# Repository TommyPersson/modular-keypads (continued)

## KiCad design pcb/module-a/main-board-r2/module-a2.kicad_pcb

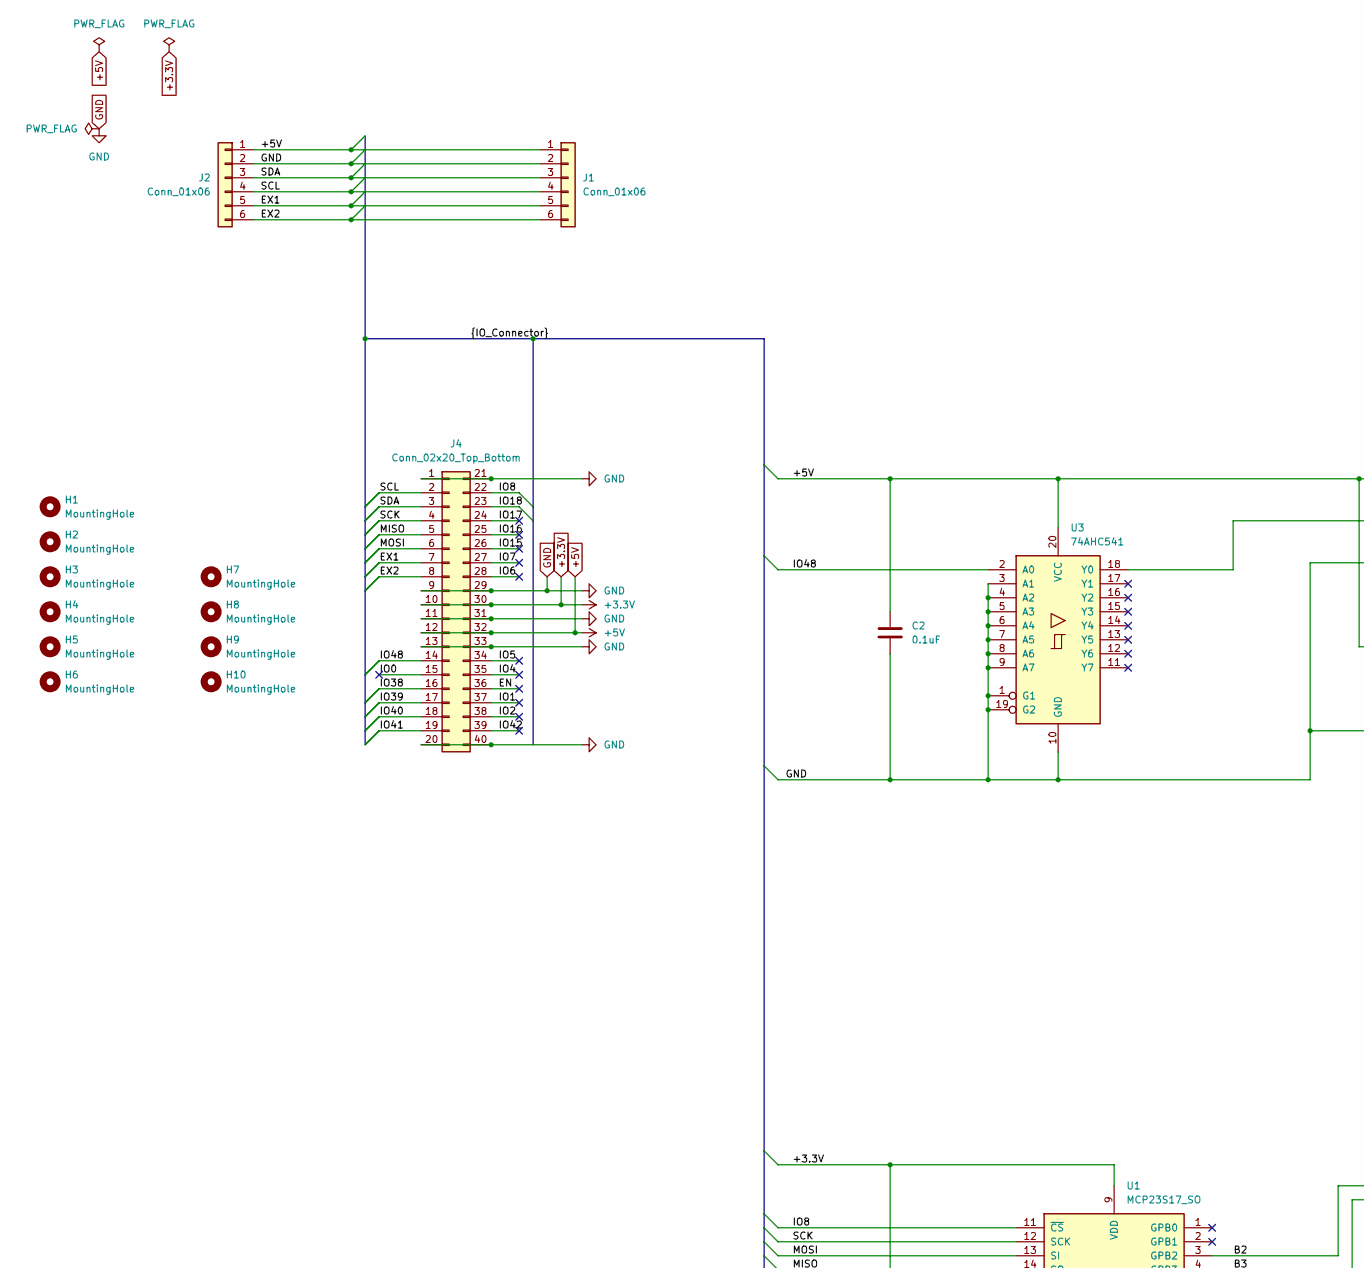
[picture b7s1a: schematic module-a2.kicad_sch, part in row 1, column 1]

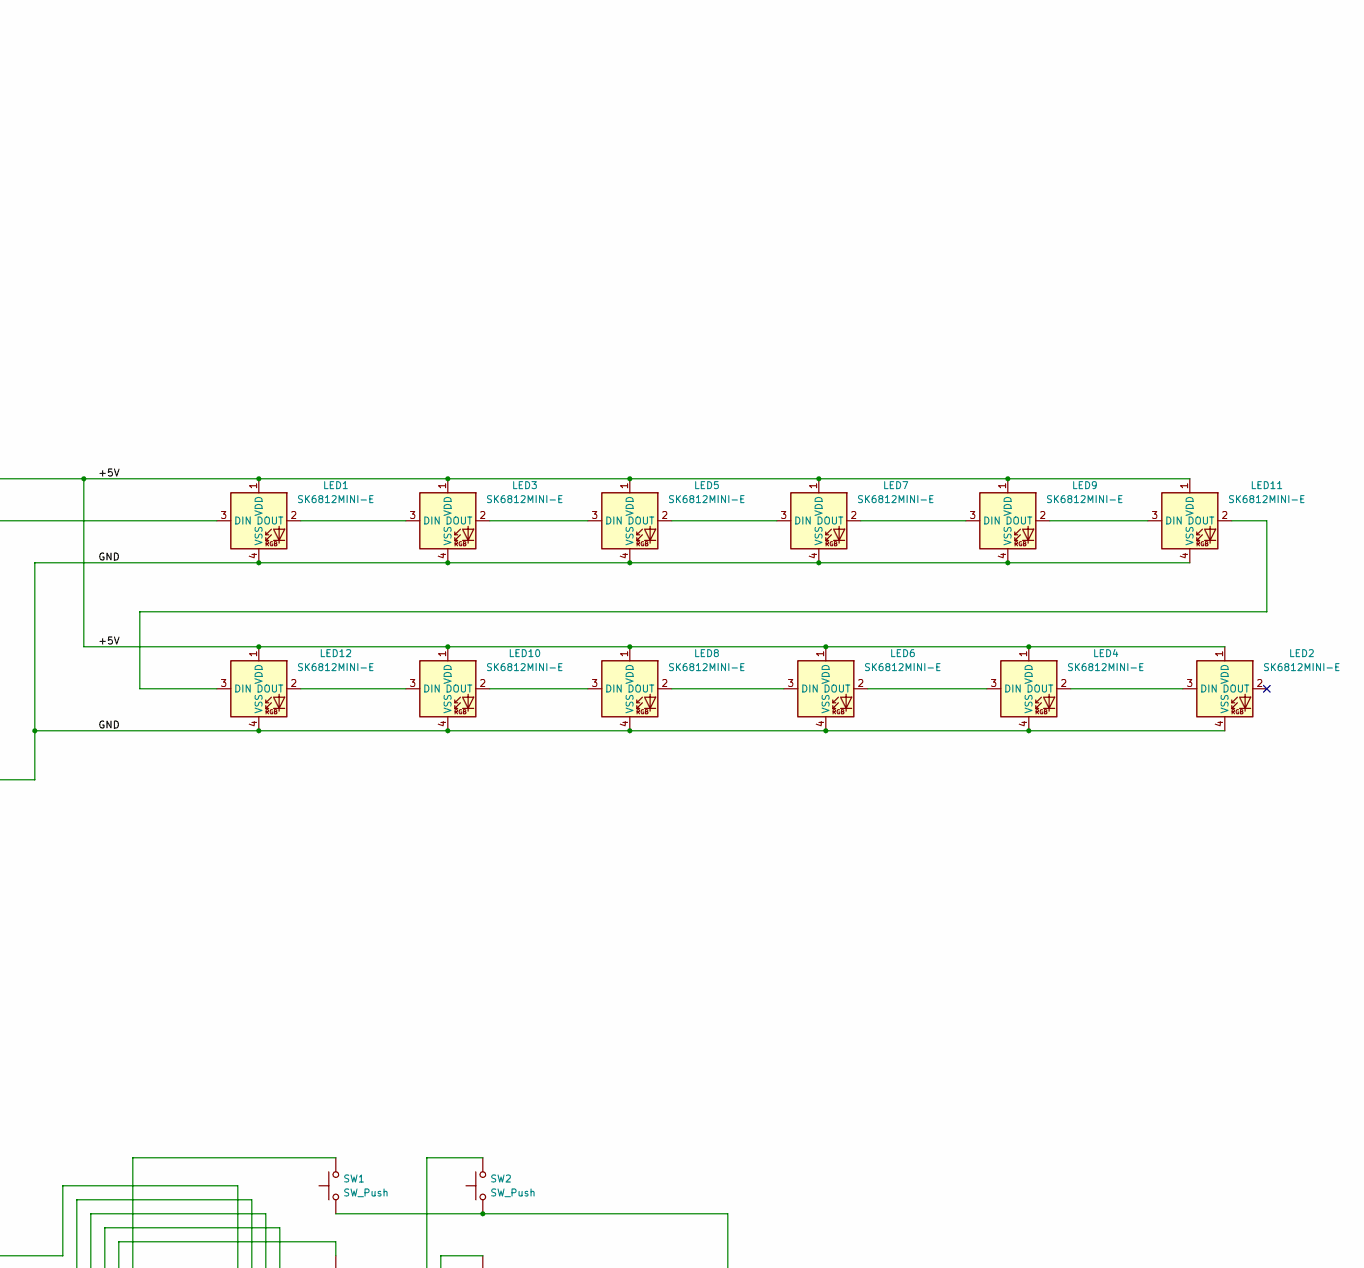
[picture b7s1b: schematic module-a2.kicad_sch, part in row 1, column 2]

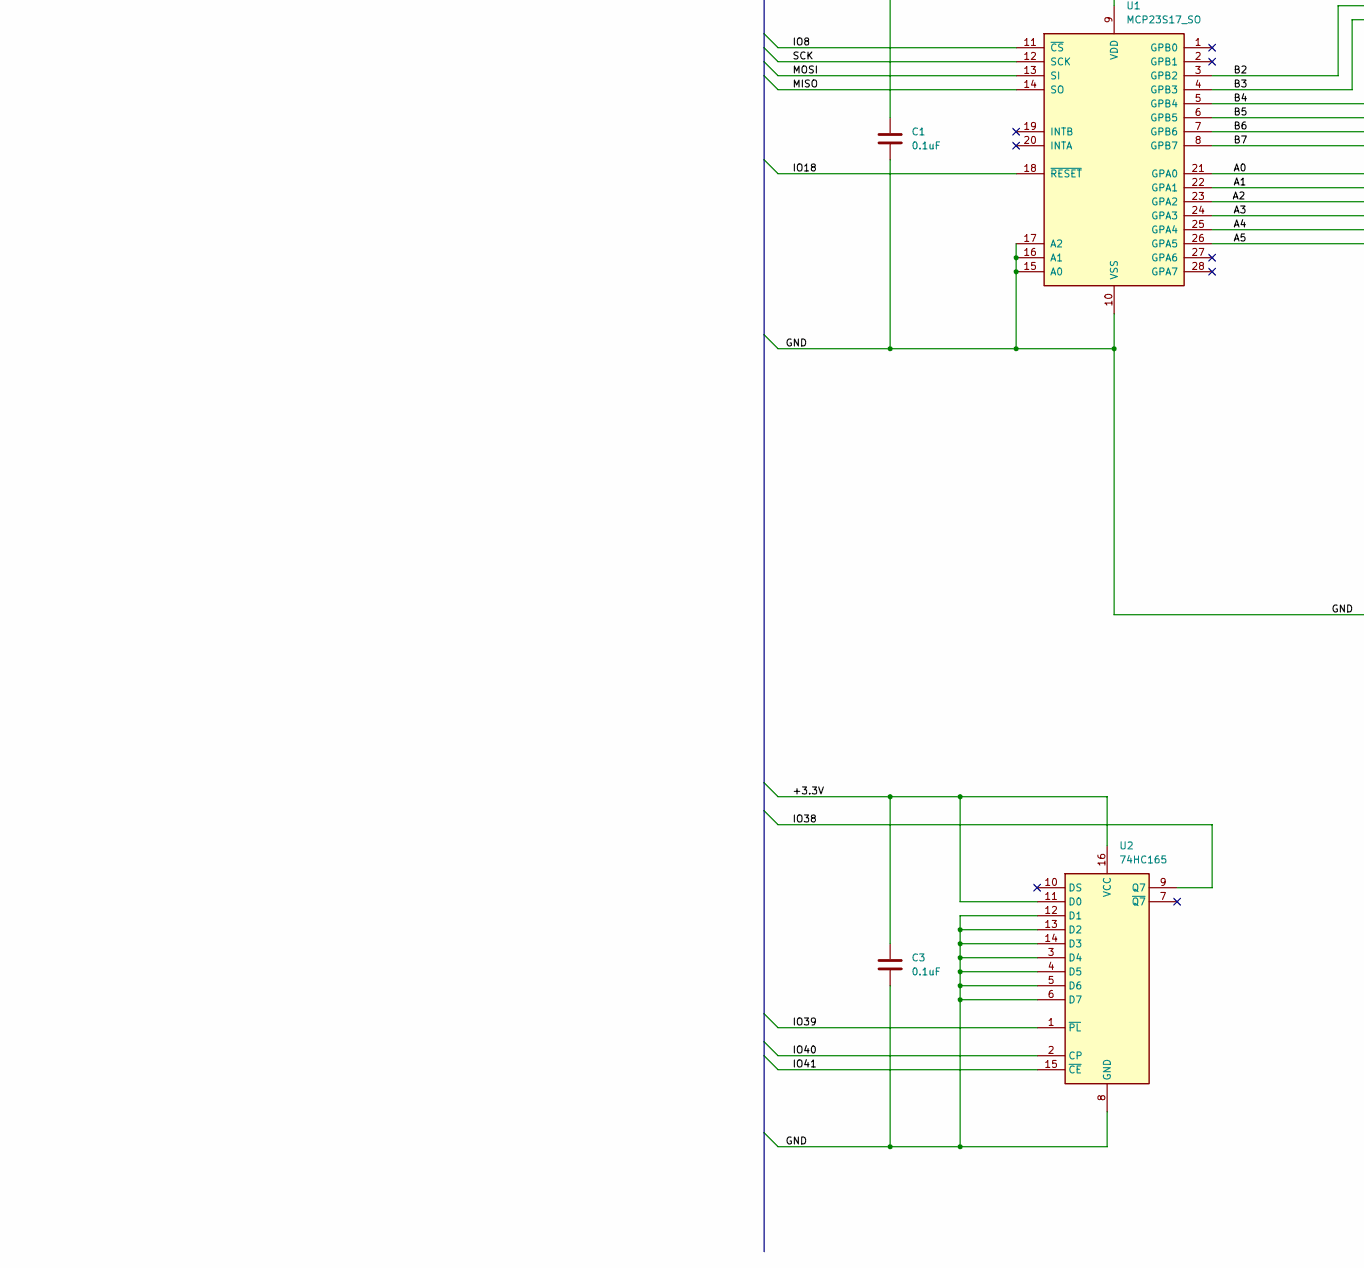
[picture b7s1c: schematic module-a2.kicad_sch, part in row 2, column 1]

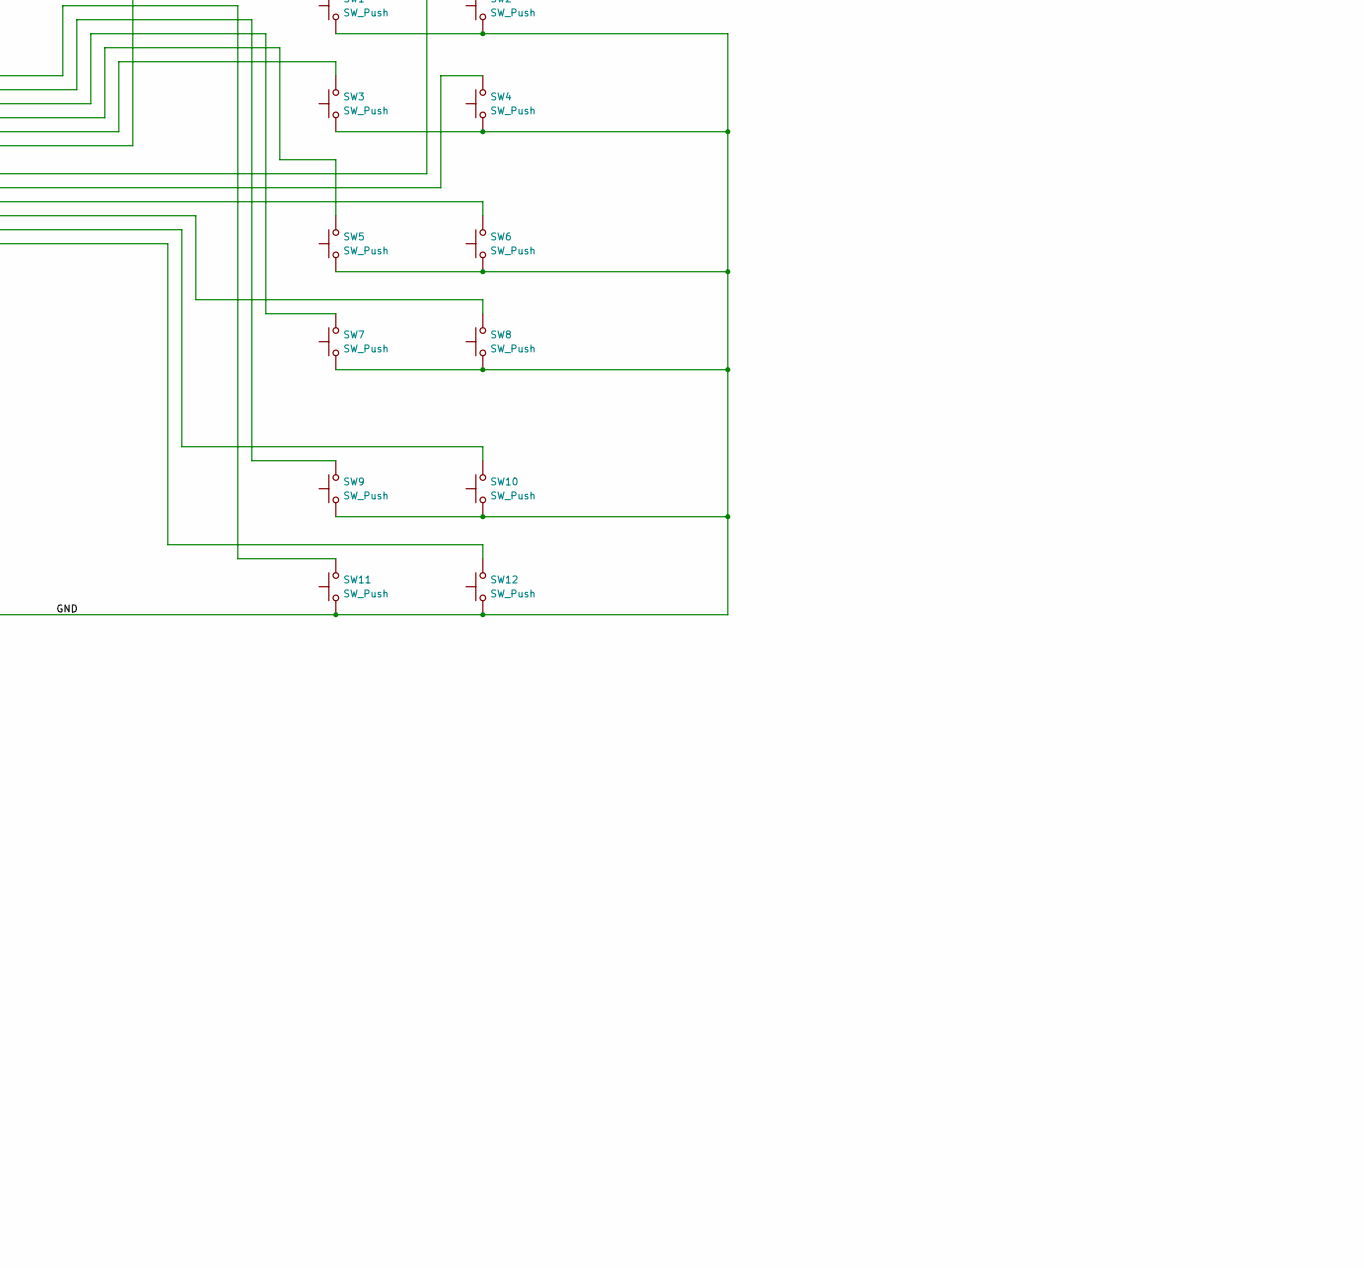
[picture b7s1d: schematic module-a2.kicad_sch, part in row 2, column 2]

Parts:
C1, C2, C3: 0.1uF; C_1206_3216Metric_Pad1.33x1.80mm_HandSolder
H1, H2, H3, H4, H5, H6: MountingHole; MountingHole_2.2mm_M2
H7, H8, H9, H10: MountingHole; MountingHole_3.7mm_Pad_TopOnly
J1: Conn_01x06; PinSocket_1x06_P2.54mm_MagPogoHor
J2: Conn_01x06; PinSocket_1x06_P2.54mm_MagPogoHor_R
J4: Conn_02x20_Top_Bottom; Hirose_DF12_DF12E3.0-40DP-0.5V_2x20_P0.50mm_Vertical
LED1, LED2, LED3, LED4, LED5, LED6, LED7, LED8, LED9, LED10, LED11, LED12: SK6812MINI-E; LED_choc_6028R-ROT
SW1, SW2, SW3, SW4, SW5, SW6, SW7, SW8, SW9, SW10, SW11, SW12: SW_Push; SW_Hotswap_Kailh_Choc_V1_1.50u
U1: MCP23S17_SO; SOIC-28W_7.5x17.9mm_P1.27mm
U2: 74HC165; SOIC-16_3.9x9.9mm_P1.27mm
U3: 74AHC541; SOIC-20W_7.5x12.8mm_P1.27mm

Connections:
+3.3V: C1.1, C3.1, J4.10, J4.30, U1.9 (VDD), U2.11 (D0), U2.16 (VCC)
+5V: C2.1, J1.1, J2.1, J4.12, J4.32, LED1.1 (VDD), LED2.1 (VDD), LED3.1 (VDD), LED4.1 (VDD), LED5.1 (VDD), LED6.1 (VDD), LED7.1 (VDD), LED8.1 (VDD), LED9.1 (VDD), LED10.1 (VDD), LED11.1 (VDD), LED12.1 (VDD), U3.20 (VCC)
/A0: SW2.2, U1.21 (GPA0)
/A1: SW4.2, U1.22 (GPA1)
/A2: SW6.2, U1.23 (GPA2)
/A3: SW8.2, U1.24 (GPA3)
/A4: SW10.2, U1.25 (GPA4)
/A5: SW12.2, U1.26 (GPA5)
/B2: SW11.2, U1.3 (GPB2)
/B3: SW9.2, U1.4 (GPB3)
/B4: SW7.2, U1.5 (GPB4)
/B5: SW5.2, U1.6 (GPB5)
/B6: SW3.2, U1.7 (GPB6)
/B7: SW1.2, U1.8 (GPB7)
/EN: J4.36
/EX1: J1.5, J2.5, J4.7
/EX2: J1.6, J2.6, J4.8
/IO0: J4.15
/IO1: J4.37
/IO2: J4.38
/IO4: J4.35
/IO5: J4.34
/IO6: J4.28
/IO7: J4.27
/IO8: J4.22, U1.11 (~CS)
/IO15: J4.26
/IO16: J4.25
/IO17: J4.24
/IO18: J4.23, U1.18 (~RESET)
/IO38: J4.16, U2.9 (Q7)
/IO39: J4.17, U2.1 (~PL)
/IO40: J4.18, U2.2 (CP)
/IO41: J4.19, U2.15 (~CE)
/IO42: J4.39
/IO48: J4.14, U3.2 (A0)
/MISO: J4.5, U1.14 (SO)
/MOSI: J4.6, U1.13 (SI)
/SCK: J4.4, U1.12 (SCK)
/SCL: J1.4, J2.4, J4.2
/SDA: J1.3, J2.3, J4.3
GND: C1.2, C2.2, C3.2, J1.2, J2.2, J4.1, J4.9, J4.11, J4.13, J4.20, J4.21, J4.29, J4.31, J4.33, J4.40, LED1.4 (VSS), LED2.4 (VSS), LED3.4 (VSS), LED4.4 (VSS), LED5.4 (VSS), LED6.4 (VSS), LED7.4 (VSS), LED8.4 (VSS), LED9.4 (VSS), LED10.4 (VSS), LED11.4 (VSS), LED12.4 (VSS), SW1.1, SW2.1, SW3.1, SW4.1, SW5.1, SW6.1, SW7.1, SW8.1, SW9.1, SW10.1, SW11.1, SW12.1, U1.10 (VSS), U1.15 (A0), U1.16 (A1), U1.17 (A2), U2.3 (D4), U2.4 (D5), U2.5 (D6), U2.6 (D7), U2.8 (GND), U2.12 (D1), U2.13 (D2), U2.14 (D3), U3.1 (G1), U3.3 (A1), U3.4 (A2), U3.5 (A3), U3.6 (A4), U3.7 (A5), U3.8 (A6), U3.9 (A7), U3.10 (GND), U3.19 (G2)
unnamed: LED1.3 (DIN), U3.18 (Y0)
unnamed: LED1.2 (DOUT), LED3.3 (DIN)
unnamed: LED2.3 (DIN), LED4.2 (DOUT)
unnamed: LED3.2 (DOUT), LED5.3 (DIN)
unnamed: LED4.3 (DIN), LED6.2 (DOUT)
unnamed: LED5.2 (DOUT), LED7.3 (DIN)
unnamed: LED6.3 (DIN), LED8.2 (DOUT)
unnamed: LED7.2 (DOUT), LED9.3 (DIN)
unnamed: LED10.3 (DIN), LED12.2 (DOUT)
unnamed: LED8.3 (DIN), LED10.2 (DOUT)
unnamed: LED9.2 (DOUT), LED11.3 (DIN)
unnamed: LED11.2 (DOUT), LED12.3 (DIN)

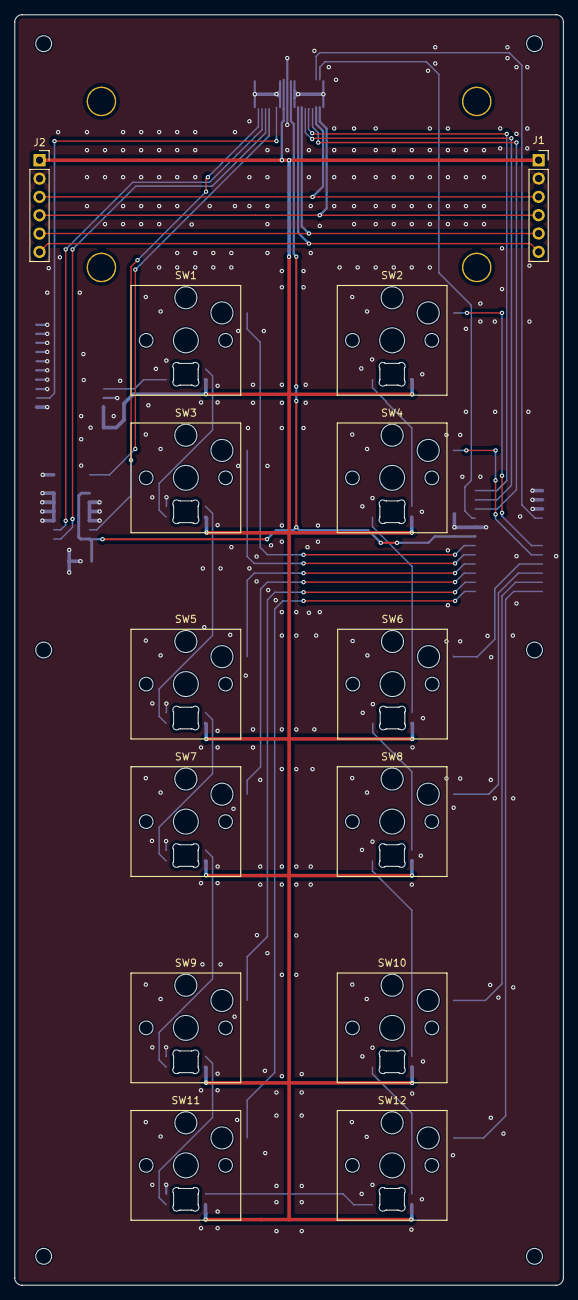
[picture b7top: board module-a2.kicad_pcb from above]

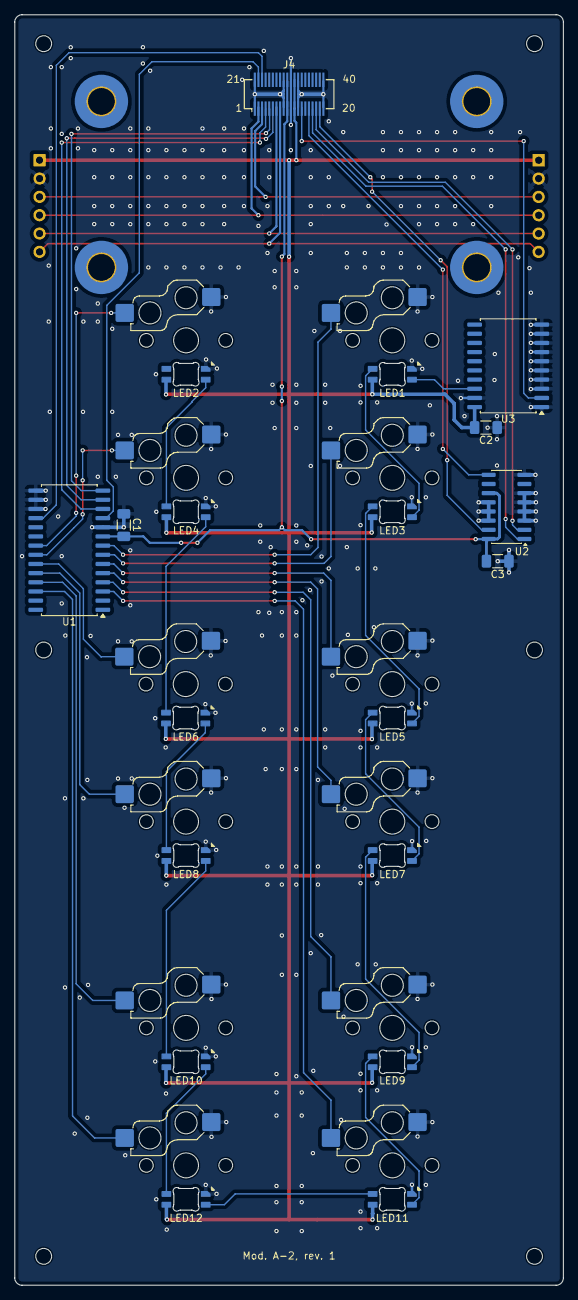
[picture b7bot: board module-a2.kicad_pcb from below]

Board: 2 copper layers, 76.0 x 176.0 mm, 43 parts (23 on the bottom side), 41 nets.

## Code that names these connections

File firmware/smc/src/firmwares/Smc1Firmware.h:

#pragma once

#include <pins_arduino.h>

#include "Firmware.h"
#include "hal/buttons/PushButtonWithIndicator.h"

namespace smc::firmwares {
    class Smc1Firmware : public Firmware {
    public:
        Smc1Firmware();
        ~Smc1Firmware() override;

        uint8_t deviceType() override { return 0x01; }

    protected:
        void doSetup() override;
        void doUpdate(uint32_t deltaUs, events::EventQueue& queue) override;
        int8_t ledIndexForButton(uint8_t buttonNumber) override;


    private:
        hal::buttons::PushButtonWithIndicator buttons[4] = {
            hal::buttons::PushButtonWithIndicator(1, PIN_PA3, leds, 0),
            hal::buttons::PushButtonWithIndicator(2, PIN_PA4, leds, 1),
            hal::buttons::PushButtonWithIndicator(3, PIN_PB0, leds, 3),
            hal::buttons::PushButtonWithIndicator(4, PIN_PB1, leds, 2),
        };
    };
}

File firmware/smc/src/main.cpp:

#include <tinyNeoPixel.h>

#include "firmwares/Firmware.h"
#include "firmwares/FirmwareFactory.h"
#include "hal/identity/DeviceId.h"
#include "hal/identity/DeviceName.h"
#include "hal/spi/SpiSlave.h"

namespace {
    auto firmwareFactory = smc::firmwares::FirmwareFactory(
        {
            .pinQ = PIN_PB3,
            .pinCLK = PIN_PB6,
            .pinCE = PIN_PB4,
            .pinLD = PIN_PB5,
        }
    );

    smc::hal::spi::SpiSlave spiSlave;
    smc::hal::identity::DeviceNameStorage deviceNameStorage;
    smc::firmwares::Firmware* firmware = nullptr;
    smc::events::EventQueue eventQueue;

    uint32_t prevUs = 0;
}

void setup() {
    Serial.swap(1);
    Serial.begin(9600);

    firmware = firmwareFactory.create();
    firmware->setup();

    uint8_t deviceId[smc::hal::identity::DEVICE_ID_LENGTH];
    smc::hal::identity::computeDeviceId(deviceId);
    spiSlave.setDeviceId(deviceId);

    uint8_t deviceName[smc::hal::identity::DEVICE_NAME_LENGTH];
    deviceNameStorage.load(deviceName);
    spiSlave.setDeviceName(deviceName);
    Serial.printf("Device name: %s\r\n", reinterpret_cast<const char*>(deviceName));

    spiSlave.setup();
    spiSlave.setDeviceType(firmware->deviceType());
    spiSlave.enqueueEvent({.type = smc::events::types::BOOTED});
}


void processCommand(const smc::hal::spi::Command& command) {
    switch (command.type) {
    case smc::hal::spi::commands::FLASH_IDENTIFICATION_LIGHTS:
        firmware->flashIdentificationLights();
        break;
    case smc::hal::spi::commands::FLASH_BUTTON_IDENTIFICATION_LIGHT:
        firmware->flashButtonIdentificationLight(command.arguments[0]);
        break;
    case smc::hal::spi::commands::WRITE_DEVICE_NAME: {
        uint8_t deviceName[smc::hal::identity::DEVICE_NAME_LENGTH];
        memcpy(deviceName, command.arguments, sizeof(deviceName));

        // Stored as given, but served normalized, the same as it will be after a restart
        deviceNameStorage.store(deviceName);
        smc::hal::identity::normalizeDeviceName(deviceName);
        spiSlave.setDeviceName(deviceName);
        break;
    }
    default:
        break;
    }
}

void loop() {
    delayMicroseconds(500);

    const auto currentUs = micros();
    const auto deltaUs = currentUs - prevUs;
    prevUs = currentUs;

    spiSlave.update(deltaUs, eventQueue);

    smc::hal::spi::Command command;
    while (spiSlave.dequeueCommand(command)) {
        processCommand(command);
    }

    firmware->update(deltaUs, eventQueue);

    if (deviceNameStorage.update()) {
        eventQueue.enqueue({.type = smc::events::types::DEVICE_NAME_STORED});
    }

    while (const auto* event = eventQueue.dequeue()) {
        spiSlave.enqueueEvent(*event);

        Serial.printf("%i %i\n\r", event->type, event->data);
    }
}

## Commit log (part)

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2025-09-14 init
2025-09-15 Extract modular firmware
2025-09-18 Add module-0 board
2025-09-20 Add module-b (rotary encoders x3)
2025-09-21 3V net should not be shared across the bus
2025-09-28 Config tool progress
2025-09-28 More module scads
2025-09-29 Implement basic device commanding structure
2025-10-02 Refactor line reading in firmware
2025-10-04 Implement command handler and various basic read commands
2025-10-09 Extract GenericFirmware and change Firmware to a base class
2025-10-09 Use standard strings
2025-10-10 Implement command argument parsing
2025-10-10 Implement device configuration commands
2025-10-11 Move basic commands to a base folder
2025-10-11 Add RegisterManager
2025-10-13 Add SwitchMonitor
2025-10-13 Add indicator leds
2025-10-14 MasterFirmware + SwitchStateNotifier + more event based switch updates
2025-10-15 Show device registers in config-tool
2025-10-16 Reorganize config tool directories
2025-10-16 Add basic router and navdrawer
2025-10-17 First device preview card
2025-10-20 Bump vite from 7.1.10 to 7.1.11 in /config-tool
    Bumps [vite](https://github.com/vitejs/vite/tree/HEAD/packages/vite) from 7.1.10 to 7.1.11.
    - [Release notes](https://github.com/vitejs/vite/releases)
    - [Changelog](https://github.com/vitejs/vite/blob/main/packages/vite/CHANGELOG.md)
    - [Commits](https://github.com/vitejs/vite/commits/v7.1.11/packages/vite)
    ---
    updated-dependencies:
2025-10-22 Implement RotationalEncoderMonitor
2025-10-23 Allow commands to return multiline responses
2025-10-25 Make it possible to give a device a name
2025-10-26 Include deviceId in notifications
2025-11-16 Bump js-yaml from 4.1.0 to 4.1.1 in /config-tool
    Bumps [js-yaml](https://github.com/nodeca/js-yaml) from 4.1.0 to 4.1.1.
    - [Changelog](https://github.com/nodeca/js-yaml/blob/master/CHANGELOG.md)
    - [Commits](https://github.com/nodeca/js-yaml/compare/4.1.0...4.1.1)
    ---
    updated-dependencies:
    - dependency-name: js-yaml
2025-12-07 Start on i2c comms
2025-12-07 Begin refactor to split device logic and device hardware
2025-12-07 Refactor FirmwareModuleM
2025-12-07 Refactor register storage to make it easier to transfer between devices later
2025-12-13 Experiment with pipe-mounted base for modules
2025-12-13 Use ServiceLocator to reduce argument list lengths
2025-12-13 Create DeviceScanner and DeviceProxy
2025-12-14 Allow loggers to be created locally instead of passed around
2025-12-14 More flexible pipe mount base
2025-12-15 Refactor firmware construction
2025-12-15 Lower the i2c packet size to stay below the available buffer
2025-12-16 Use correct notifier ID for each runtime
2025-12-16 Fix rotary encoder click crashing
2025-12-20 Start on actual USB keyboard actions
2025-12-21 Allow multi-key presses
2025-12-21 Allow string formatting in CommandResponseWriter
2025-12-21 Reorg commands
2025-12-21 More reorg
2025-12-21 Add ListConnectedDevices command
2025-12-21 Create simpler overview page
2025-12-21 Add test mode
2025-12-22 Add device capabilities
2025-12-22 Simplify register configuration
2025-12-23 Start on key bindings page
2025-12-24 Add keyboard event observer to visualize active key codes
2025-12-24 Add keyboard event log
2025-12-24 Add macro visualizers
2025-12-25 Work on macro editor dialog
2025-12-25 Allow macro edit dialog to show the content of existing macros
2025-12-26 Allow shortcuts to distinguish left and right modifier keys. Fix keyboard listener after modal closes.
2025-12-26 Split ID and name in macro definitions
2025-12-26 Add a log viewer drop-down. Start on save command
2025-12-26 Placeholder implementations for macro editing commands
2025-12-26 Bump vite from 7.1.10 to 7.3.0 in /config-tool
    Bumps [vite](https://github.com/vitejs/vite/tree/HEAD/packages/vite) from 7.1.10 to 7.3.0.
    - [Release notes](https://github.com/vitejs/vite/releases)
    - [Changelog](https://github.com/vitejs/vite/blob/v7.3.0/packages/vite/CHANGELOG.md)
    - [Commits](https://github.com/vitejs/vite/commits/v7.3.0/packages/vite)
    ---
    updated-dependencies:
2025-12-26 Read stored macros from the file system
2025-12-27 Implement real saving of macros
2025-12-27 Add macro deletion
2025-12-27 Port command infra from other projects
2025-12-29 Create stubbed interactions for keybinding selections
2025-12-30 Fix react warnings
2025-12-30 Implement stubbed key binding storage in firmware
2025-12-30 Implement key binding storage
2025-12-30 Implement full chain for push button key bindings
2025-12-30 Implement rotary encoder key bindings fully
2025-12-31 Add DeviceComand interface to allow shrinking the DeviceFacade
2025-12-31 Add metrics drop down
2025-12-31 Move most DeviceFacade methods to individual DeviceCommand implementations
2025-12-31 Add UI for editing consumer control code macros
2025-12-31 Implement ConsumerControl macros
2026-01-01 Generialize macro data serialization in firmware
2026-01-01 Re-index parts passed to serializers to simplify access
2026-01-01 Implement SystemControl actions
2026-01-01 Add MacroTypeDefinition to get various switch-cases in frontend
2026-01-01 Extract macro-related code from 'key-bindings' directory
2026-01-01 Improve error handling for device commands
2026-01-02 Add file system metrics
2026-01-02 Remove old code
2026-01-02 Move frameworky stuff to utils/ instead of firmwares/common
2026-01-02 Move frameworky stuff to utils/ instead of firmwares/common #2
2026-01-02 Adjust some utils namespaces
2026-01-02 More namespace adjustments
2026-01-02 Yet more namespacing
2026-01-02 Avoid heap allocation in LineStreamer
2026-01-02 Avoid heap allocations during read macros flow
2026-01-02 Avoid allocations during read key-bindings flow
2026-01-03 Move i2c package to utils
2026-01-03 Move device endpoint definitions out of utils
2026-01-03 Simplify usage of i2c Client
2026-01-03 Make metrics more flexible
2026-01-03 Add macro and keybinding metrics
2026-01-03 Add timer metric for device looper. increase i2c speed and lower the number of requested device registers
2026-01-03 Add time utils to abstract platform specific functions
2026-01-04 Create simple jig to hold side connectors in place while soldering
2026-01-05 Fix name memory corruption when saving macros. Escape macro names to allow special characters
2026-01-05 Forward esp system logs, but not as regular logs
2026-01-05 Implement typing macro
2026-01-05 Minimize the amount of data synced during register refresh
2026-01-05 Implement infra for generic i2c command handling
2026-01-06 Begin on "enable identification lights" feature
2026-01-06 Create a simple pulsing animation for device identification
2026-01-06 Rename commands for consistency
2026-01-06 Rename i2c commands to "RemoteCommand[...]" to distinguish them
2026-01-06 Move local/remote logic to DeviceModule base class
2026-01-06 Implement remote device renaming
2026-01-08 Add individual button identification command
2026-01-09 Bump react-router from 7.9.4 to 7.12.0 in /config-tool
    Bumps [react-router](https://github.com/remix-run/react-router/tree/HEAD/packages/react-router) from 7.9.4 to 7.12.0.
    - [Release notes](https://github.com/remix-run/react-router/releases)
    - [Changelog](https://github.com/remix-run/react-router/blob/main/packages/react-router/CHANGELOG.md)
    - [Commits](https://github.com/remix-run/react-router/commits/react-router@7.12.0/packages/react-router)
    ---
    updated-dependencies:
2026-01-09 Create new pipe mount models
2026-01-10 Fix duplicate command id
2026-01-10 Don't show buttons without LEDs as flashable
2026-01-24 New pcbs, seperated out a compute/io board
2026-01-24 scad for connector placing jig
2026-03-01 New pcbs
2026-03-01 Extend available hid bindings with more consumer control codes
2026-03-02 Adapt to new pcb
2026-03-02 Add a simple keycap design
2026-05-02 Reorg utils into tfw directory
2026-05-02 Add scad models
2026-05-02 Extract tfw directory to separate library. Merge all libraries into tfw
2026-05-02 Degeneralize SPI serialbus
2026-05-02 Adjust spi namespace
2026-05-02 Adjust more namespaces
2026-05-09 Move SwitchMonitor to tfw::hal, change to Button terminology inside library
2026-05-09 Move RotationalEncoder to tfw::hal, change terminology to RotaryEncoder
2026-06-27 Add workflow to build and deploy config-tool container
2026-06-28 Add basic ..gitignore for root directory
2026-06-28 test using playwright
2026-06-28 Group macros by "directory" in EditMacrosCard
2026-06-28 Group by directory in macro selector in EditKeyBindingsCard
2026-06-28 Also publish docker latest tag
